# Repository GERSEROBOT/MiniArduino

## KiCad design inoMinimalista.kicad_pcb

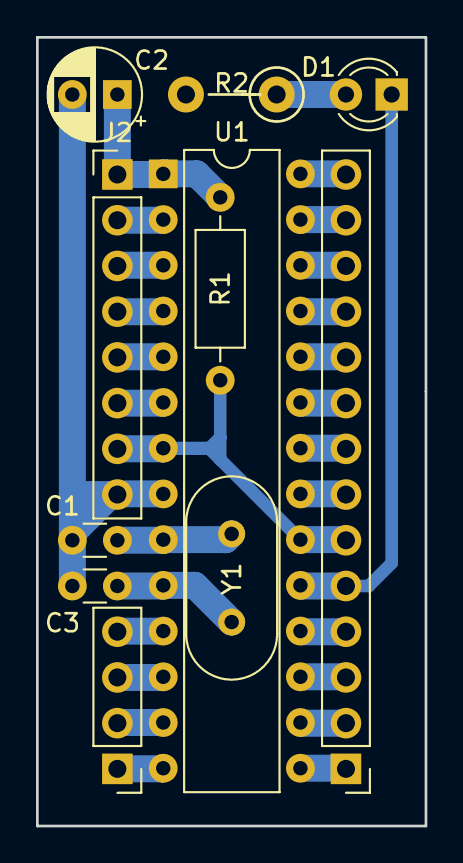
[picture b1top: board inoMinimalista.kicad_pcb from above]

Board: 2 copper layers, 21.6 x 43.8 mm, 11 parts (0 on the bottom side), 26 nets.

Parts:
C1, C3: 22pF; C_Disc_D3.0mm_W1.6mm_P2.50mm
C2: 0u1F; CP_Radial_D5.0mm_P2.50mm
D1: LED_ALT; LED_D3.0mm
J1: 16-28; PinHeader_1x14_P2.54mm_Vertical
J2: PD; PinHeader_1x08_P2.54mm_Vertical
J3: PD; PinHeader_1x04_P2.54mm_Vertical
R1: 10k; R_Axial_DIN0207_L6.3mm_D2.5mm_P10.16mm_Horizontal
R2: 330; Resistor_Vertical_RM3mm
U1: ATmega328P-PU; DIP-28_W7.62mm
Y1: Crystal; Crystal_HC18-U_Vertical

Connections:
+5V: J1.6, J2.7, R1.1, U1.7, U1.20
Earth: C1.2, C2.2, C3.2, J1.7, J1.8, J2.8, R2.2, U1.8, U1.21, U1.22
unnamed: D1.2, R2.1
PB0: J3.1, U1.14
PB1: J1.1, U1.15
PB2: J1.2, U1.16
PB3: J1.3, U1.17
PB4: J1.4, U1.18
PB5: D1.1, J1.5, U1.19
PB7: J3.2, U1.13
PC0: J1.9, U1.23
PC1: J1.10, U1.24
PC2: J1.11, U1.25
PC3: J1.12, U1.26
PC4: J1.13, U1.27
PC5: J1.14, U1.28
PD0: J2.2, U1.2
PD1: J2.3, U1.3
PD2: J2.4, U1.4
PD3: J2.5, U1.5
PD4: J2.6, U1.6
PD5: J3.4, U1.11
PD6: J3.3, U1.12
RST: C2.1, J2.1, R1.2, U1.1
XTL1: C1.1, U1.9, Y1.1
XTL2: C3.1, U1.10, Y1.2
